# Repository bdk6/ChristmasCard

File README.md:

# ChristmasCard
Electronic Christmas Card

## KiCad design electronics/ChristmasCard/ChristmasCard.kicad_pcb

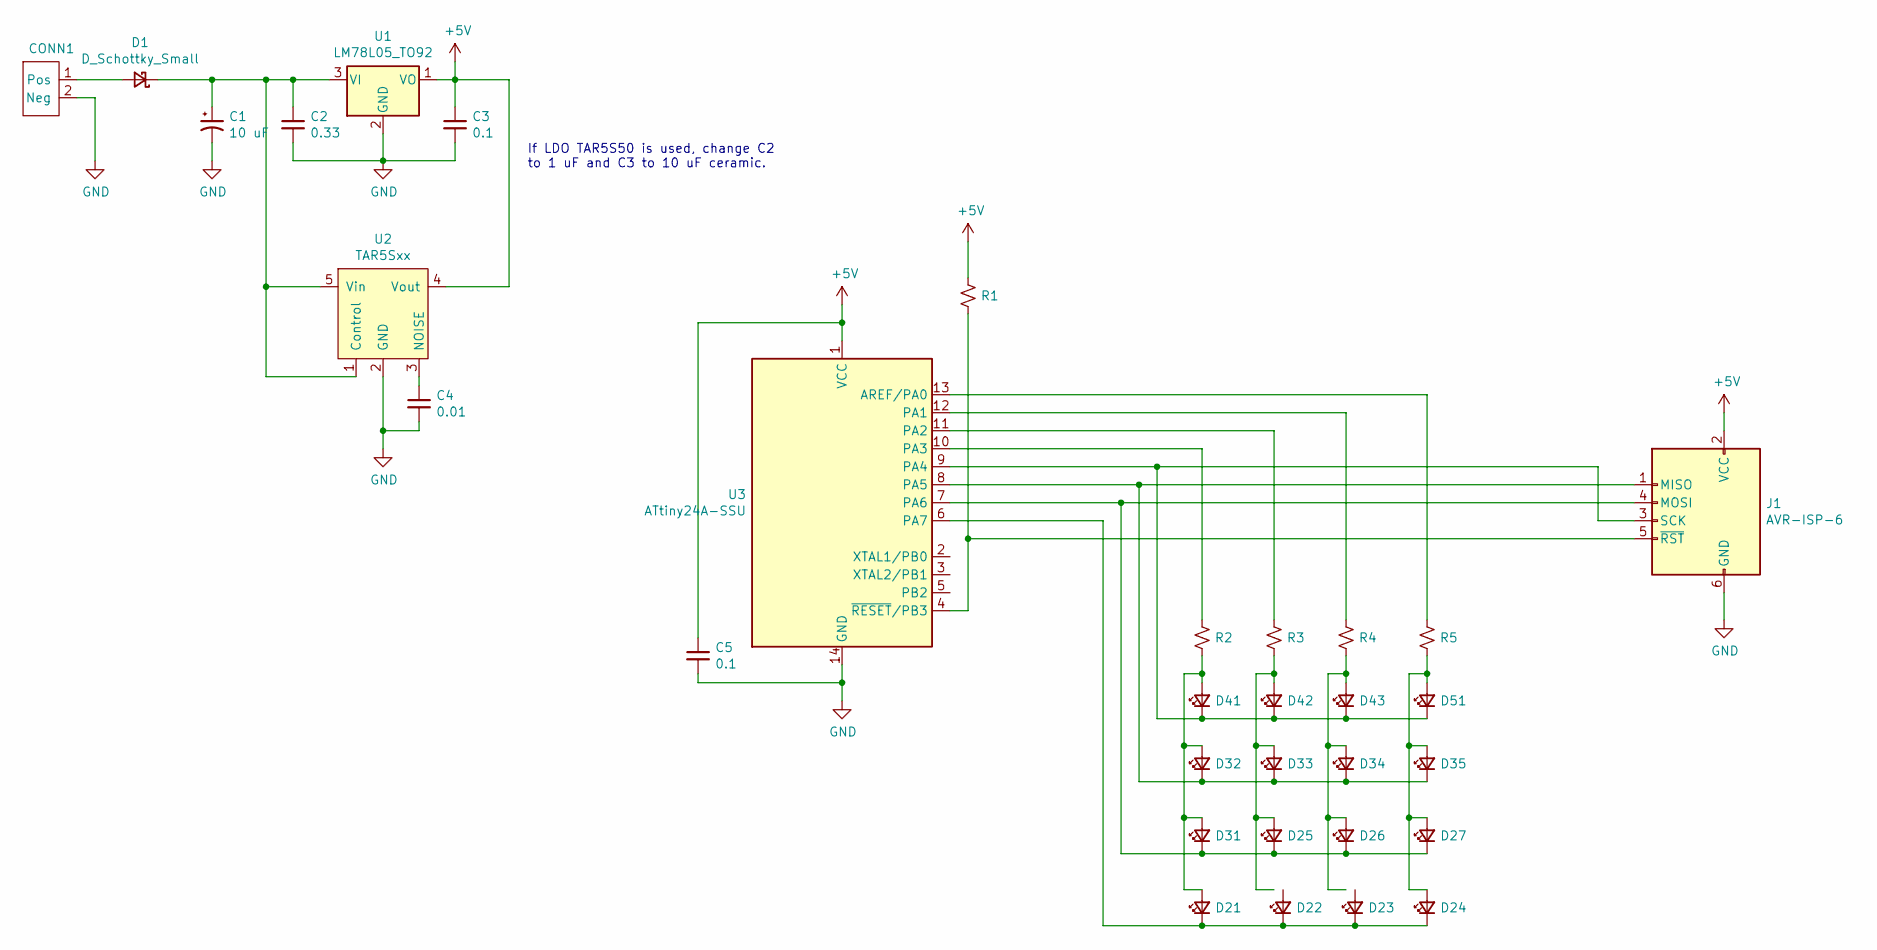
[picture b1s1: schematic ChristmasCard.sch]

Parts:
C1: 10 uF; CP_Radial_D8.0mm_P5.00mm
C2: 0.33; C_Disc_D4.3mm_W1.9mm_P5.00mm
C3, C5: 0.1; C_Disc_D4.3mm_W1.9mm_P5.00mm
C4: 0.01; C_Disc_D4.3mm_W1.9mm_P5.00mm
CONN1: PCB_Mount_9V_connector_Keystone_968; Keystone_968_9V_snap
D1: D_Schottky_Small; D_DO-41_SOD81_P10.16mm_Horizontal
D21, D22, D23, D24, D25, D26, D27, D31, D32, D33, D34, D35, D41, D42, D43, D51: LED; LED_D5.0mm
J1: AVR-ISP-6; PinHeader_2x03_P2.54mm_Vertical
R1: 100K; R_Axial_DIN0207_L6.3mm_D2.5mm_P10.16mm_Horizontal
R2, R3, R4, R5: 3K; R_Axial_DIN0207_L6.3mm_D2.5mm_P10.16mm_Horizontal
U1: LM78L05_TO92; TO-92_Inline
U2: TAR5Sxx; TSOP-5_1.65x3.05mm_P0.95mm
U3: ATtiny24A-SSU; SOIC-14_3.9x8.7mm_P1.27mm

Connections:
+5V: C3.1, C5.1, J1.2 (VCC), R1.1, U1.1 (VO), U2.4 (Vout), U3.1 (VCC)
GND: C1.2, C2.2, C3.2, C4.2, C5.2, CONN1.2 (Neg), J1.6 (GND), U1.2 (GND), U2.2 (GND), U3.14 (GND)
unnamed: C1.1, C2.1, D1.1 (K), U1.3 (VI), U2.1 (Control), U2.5 (Vin)
unnamed: C4.1, U2.3 (NOISE)
unnamed: CONN1.1 (Pos), D1.2 (A)
unnamed: D21.1 (K), D22.1 (K), D23.1 (K), D24.1 (K), U3.6 (PA7)
unnamed: D21.2 (A), D31.2 (A), D32.2 (A), D41.2 (A), R2.2
unnamed: D24.2 (A), D27.2 (A), D35.2 (A), D51.2 (A), R5.2
unnamed: D25.1 (K), D26.1 (K), D27.1 (K), D31.1 (K), J1.4 (MOSI), U3.7 (PA6)
unnamed: D25.2 (A), D33.2 (A), D42.2 (A), R3.2
unnamed: D26.2 (A), D34.2 (A), D43.2 (A), R4.2
unnamed: D32.1 (K), D33.1 (K), D34.1 (K), D35.1 (K), J1.1 (MISO), U3.8 (PA5)
unnamed: D41.1 (K), D42.1 (K), D43.1 (K), D51.1 (K), J1.3 (SCK), U3.9 (PA4)
unnamed: J1.5 (~RST), R1.2, U3.4 (~RESET~/PB3)
unnamed: R2.1, U3.10 (PA3)
unnamed: R3.1, U3.11 (PA2)
unnamed: R4.1, U3.12 (PA1)
unnamed: R5.1, U3.13 (AREF/PA0)

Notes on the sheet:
If LDO TAR5S50 is used, change C2 to 1 uF and C3 to 10 uF ceramic.

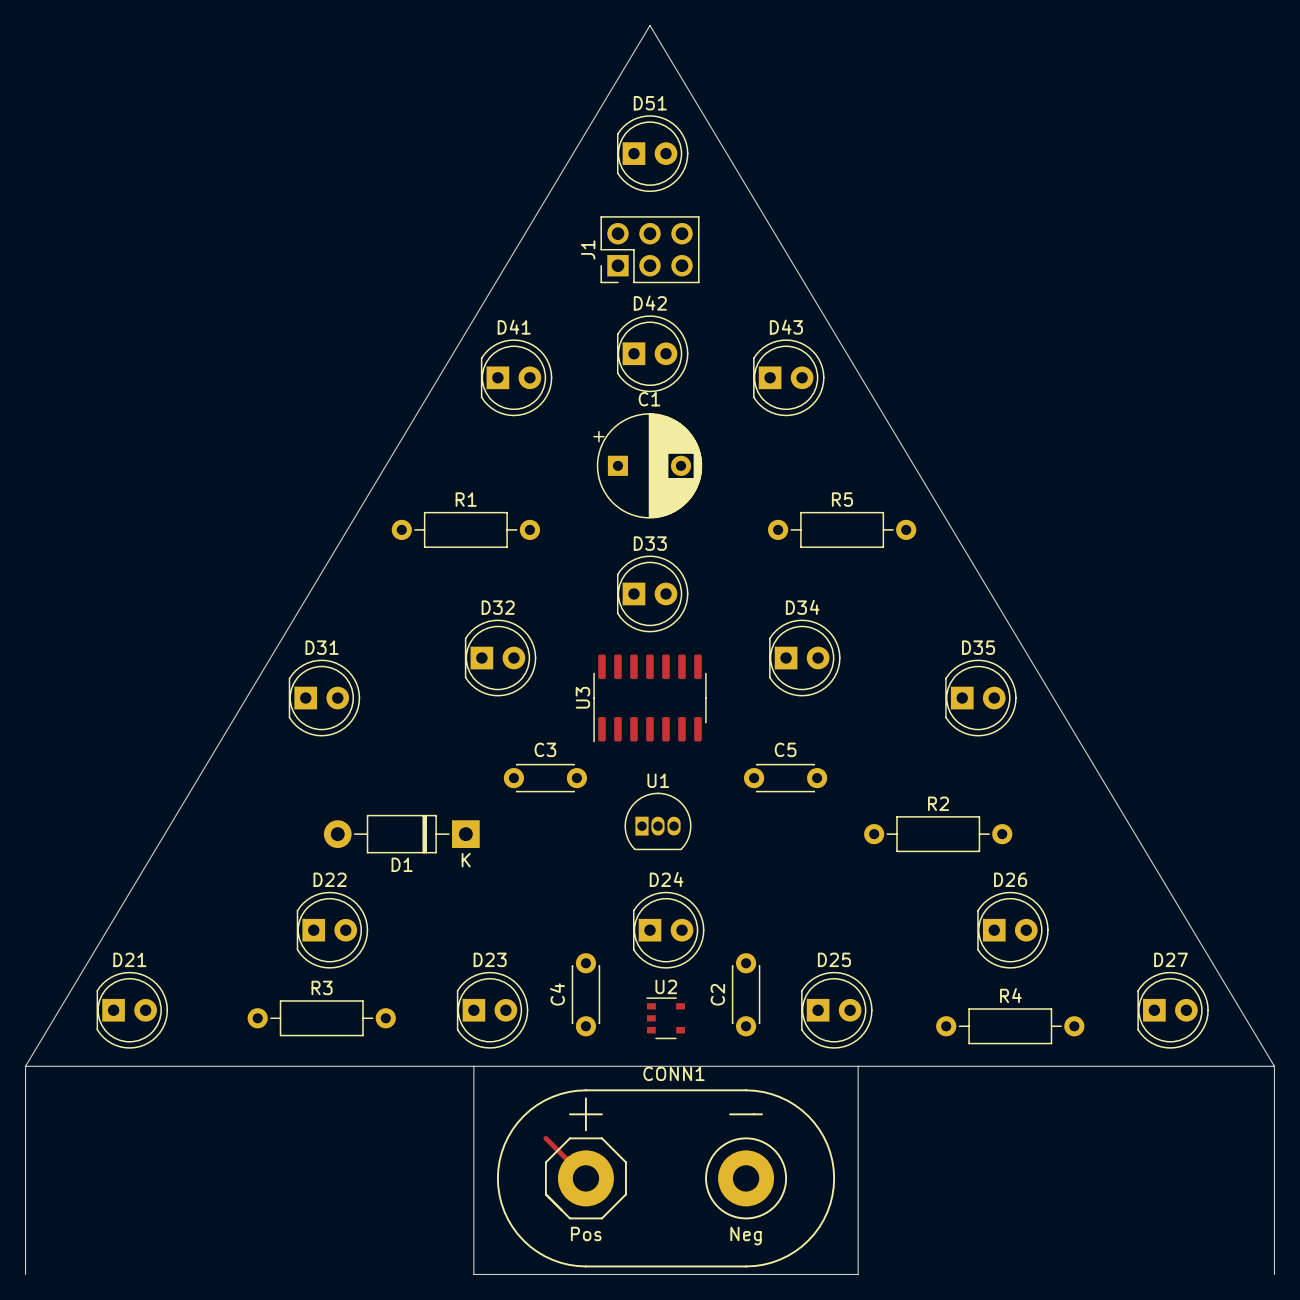
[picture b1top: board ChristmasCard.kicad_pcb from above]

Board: 2 copper layers, 99.1 x 99.1 mm, 32 parts (0 on the bottom side), 18 nets.

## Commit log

2022-08-30 Schematic and PCB with all LEDs.
2026-06-12 Added kicad files.
